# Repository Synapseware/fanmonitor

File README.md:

fanmonitor
==========

A simple temperature sensor to control fan speed in a computer case.  Has USB interface for data retrieval.

Note: The initial design of this board is totally busted.  Do not duplicate or you will waste parts.

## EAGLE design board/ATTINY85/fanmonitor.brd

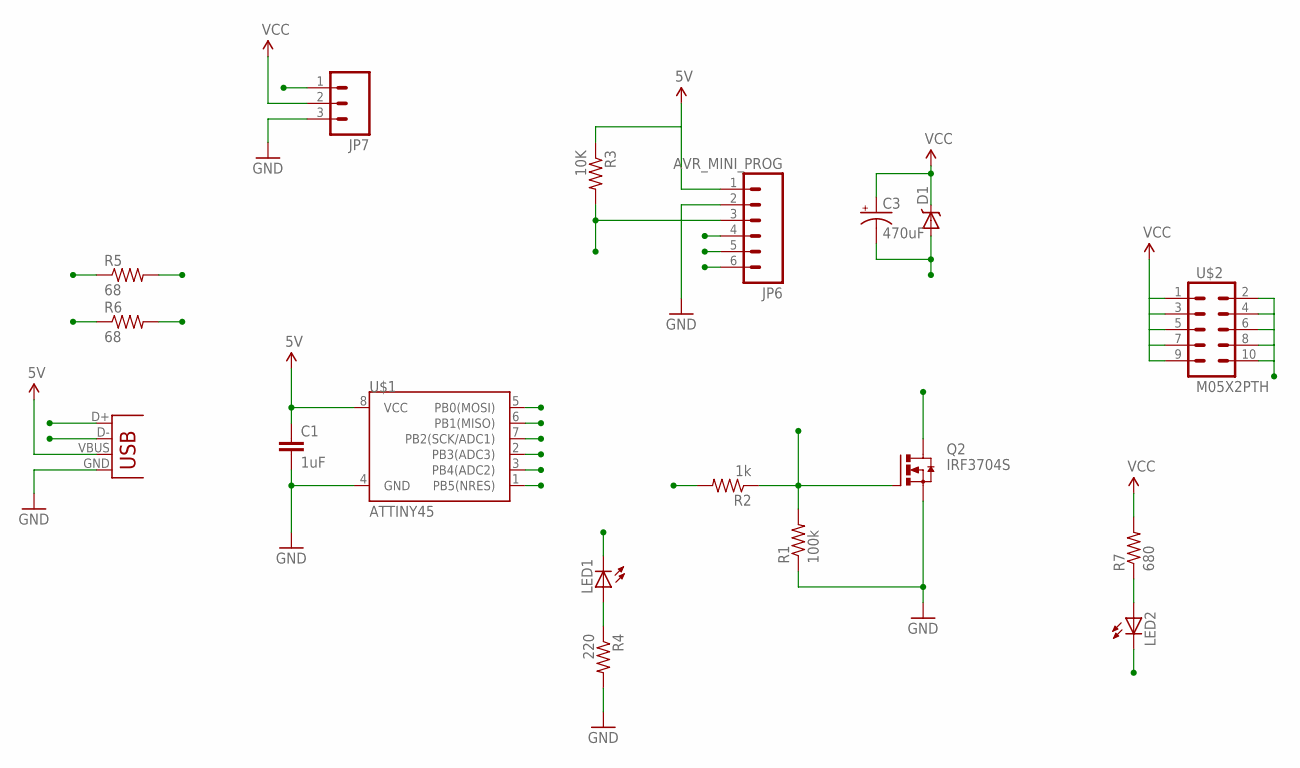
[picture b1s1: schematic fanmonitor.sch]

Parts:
C1: 1uF; 0603-CAP
C3: 470uF; PANASONIC_D
D1: DIODE-SCHOTTKY_; SMA-DIODE
JP6: AVR_MINI_PROG; 1X06
JP7: M03PTH; 1X03
LED1, LED2: LED0603; LED-0603
Q2: IRF3704S; D2PACK
R1: 100k; 0603-RES
R2: 1k; 0603-RES
R3: 10K; 0603-RES
R4: 220; 0603-RES
R5, R6: 68; 0603-RES
R7: 680; 0603-RES
U$1: ATTINY45; SO08-EIAJ
U$2: M05X2PTH; AVR_ICSP
X1: USBSMD; USB-MINIB

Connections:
5V: C1.1, JP6.1, R3.1, U$1.8 (VCC), X1.VBUS
/RST: JP6.3, R3.2, U$1.1 (PB5(NRES))
D+: R5.1, X1.D+
D-: R6.1, X1.D-
GND: C1.2, JP6.2, JP7.3, Q2.3 (S), R1.1, R4.2, U$1.4 (GND), X1.GND
MISO: JP6.6, R6.2, U$1.6 (PB1(MISO))
MOSI: JP6.4, R5.2, U$1.5 (PB0(MOSI))
unnamed: LED1.A, R4.1
unnamed: LED2.A, R7.1
PWM: R2.2, U$1.2 (PB3(ADC3))
PWM_OUT: C3.-, D1.A, LED2.C, Q2.2 (D), U$2.2, U$2.4, U$2.6, U$2.8, U$2.10
SCK: JP6.5, U$1.7 (PB2(SCK/ADC1))
SPD: JP7.1, Q2.1 (G), R1.2, R2.1
STAT: LED1.C, U$1.3 (PB4(ADC2))
VCC: C3.+, D1.C, JP7.2, R7.2, U$2.1, U$2.3, U$2.5, U$2.7, U$2.9

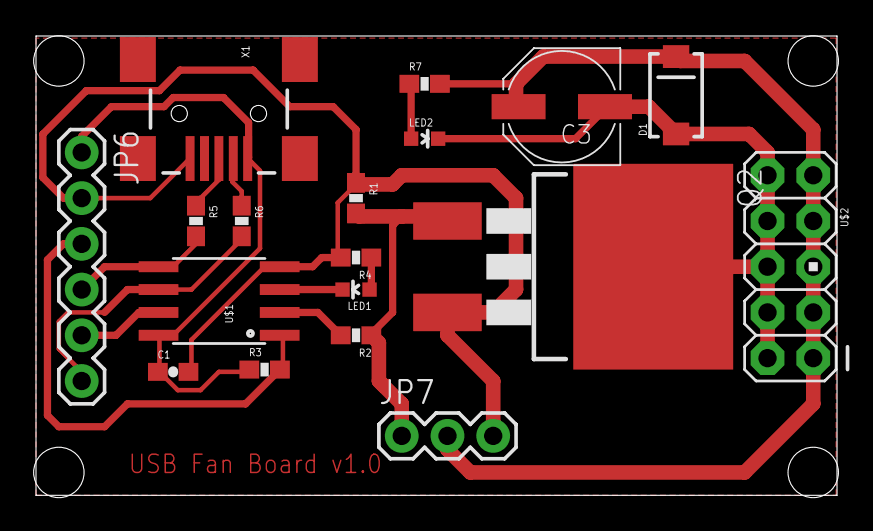
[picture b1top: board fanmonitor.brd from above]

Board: 2 copper layers, 44.5 x 25.5 mm, 18 parts (0 on the bottom side), 15 nets.

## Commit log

2014-06-02 Initial commit of fanmonitor project. Migrated from Electonics
2014-06-03 Cleaning up board files
2014-06-07 Working on linux build
2014-06-07 Build now works on linux for v-usb

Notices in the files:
parts and their libraries:
SparkFun-DigitalIC: Licensing: CC v3.0 Share-Alike You are welcome to use this library for commercial purposes.
